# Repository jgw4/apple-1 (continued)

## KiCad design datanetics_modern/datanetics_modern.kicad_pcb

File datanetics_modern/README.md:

# Replica Datanetics Keyboard

Do you need a Datanetics ASCII keyboard for your computer project (such as a replica Apple 1)? Don't want to pay high prices for an original Datanetics keyboard? Then consider building this replica.

This is not the first replica Datanetics keyboard. Mike Willegal [designed one](http://www.willegal.net/appleii/apple1-datanetics.htm). In fact, I started with his design and redid it using KiCad. Instead of using the expensive, fragile, and hard-to-find MM5740 keyboard chip, I switched to a more common microcontroller: the ATMega644P. I also removed the output buffer chips--just in case you want to redo my firmware and implement some other keyboard protocol, you'll be able to control the pin direction.

Here are the design files. The BOM does not include manufacturer part numbers because it uses very common through hole parts that you might already have. The key switches are standard Cherry MX and are available from a wide variety of sources.

[Schematic](https://github.com/schlae/replica-datanetics/blob/main/Apple1Keyb.pdf)

[Bill of Materials](https://github.com/schlae/replica-datanetics/blob/main/Apple1Keyb.csv)

[Fab Files](https://github.com/schlae/replica-datanetics/blob/main/fab/Apple1Keyb_Rev1.zip)

[Water Slide Decal Graphics](https://github.com/schlae/replica-datanetics/blob/main/keycaps.svg)

## Fabrication and Assembly Notes

The circuit board is a 2-layer board, 11.75 by 5.5 inches (298.5 x 139.7mm). No special edge connector plating or bevel is needed. To make the board look like the original, order the board "bare bones" with no solder mask or silkscreen.

**Caution: There is a "matrix" via area in the upper left corner of the board with 76 non-plated vias. The drill locations for these are included in the "Apple1Keyb-NPTH.drl" file in the fab package. The User Comments layer also includes a note to the fab vendor to NOT plate these holes. You may want to add an extra comment to your fab vendor when you put in the order that these 76 holes must not be plated.**

To assemble the board, just solder in the components. I'd recommend using a socket for the U1 microcontroller so that you can reprogram it later. The NE555 timer (U2) in the original design was meant to provide the clock for the MM5740 chip, but isn't necessary in this design. You can install it or leave it out.

The second NE555 timer (U3) is necessary for the key repeat function.

## Key Caps

The keyboard design uses standard Cherry MX key switches and keycaps are available from numerous sources. For my own build, I used DSA keycaps along with an 8U spacebar from PMK. I looked into a number of ways of putting the legends on the keycaps but I ended up having some water slide decals custom made. See the file above if you want to use this same file, but I'd recommend putting the legends closer together so they'll fit on a smaller sheet, saving you money.

## Matrix Via Area

The Datanetics design has four key switches that are not connected to the key scanning matrix and are brought out to individual pins on the edge connector. If you're building an Apple 1, you'll want to use two of these keys for the reset and clear screen functions. 

If you want keys to be included in the scanning matrix, you'll want to solder a fine wire through the appropriate via in the upper left corner of the board. To find out which key will be generated, look up the row and column number in the key\_rom array in firmware source code. You can, of course, customize the generated key by editing the source and recompiling.

## Firmware

The firmware is designed for the ATMega644P microcontroller, but it should be possible to modify it to work with other 40-pin microcontrollers in the ATMega family. The prebuilt firmware behaves like a stock MM5740.

[Prebuilt Firmware](https://github.com/schlae/replica-datanetics/blob/main/fw/apple1keyb.hex)

Be sure to set the fuse bits of the ATMega644P according to the fuses.conf file:

```
lfuse = 0x62
hfuse = 0xdd
efuse = 0xfc
```

You can build the firmware yourself pretty easily. Under Ubuntu, install the `gcc-avr` package, and build the firmware by going to the directory and typing `make`.

If you have a minipro programmer (TL866 etc) you can program the device by typing `make fuses` followed by `make prog`. For this to work correctly, you'll need the [minipro software](https://gitlab.com/DavidGriffith/minipro) installed. You could also use the Windows minipro software from the manufacturer, or another programmer entirely.

## Mechanical Brackets

[Mike Willegal's site](http://www.willegal.net/appleii/apple1-datanetics.htm) has drawings for a mechanical bracket.

## Connecting to an Apple 1

If you want to connect this keyboard to an Apple 1, you can use the following wiring diagram. The connector to use is a 30-pin 0.156" edge connector, something like EDAC 305-030-520-202 or equivalent. The DIP plug is an insulation displacement connector, something like CW CWR-130-16-0001 or equivalent.

| Edge connector pin | Description | DIP plug pin |
|--------------------|-------------|--------------|
| A | No connect (was -12V) | 11 (-12V) |
| B | Data bit 6 | 7 (B6) |
| C | Data bit 5 | 6 (B5) |
| D | Data bit 4 | 2 (B4) |
| E | Data bit 1 | 5 (B1) |
| F | Data bit 2 | 4 (B2) |
| H | Data bit 3 | 3 (B3) |
| J | Reset key | 1 (Reset) |
| K | Reset key | 9 (Gnd) |
| L | No connect (was OE) | No connect |
| M | Strobe | 14 (Str) |
| N | Data bit 7 | 8 (B7) |
| P | Data bit 8 | No connect |
| R | No connect (was data bit 9) | No connect |
| S | Ground | 9 |
| 1 | No connect | |
| 2 | No connect | |
| 3 | No connect | |
| 4 | +5V | 15, 16 |
| 5 | No connect | |
| 6 | No connect | |
| 7 | No connect | |
| 8 | Extra key 4 | 12 (Clr) |
| 9 | Extra key 4 | 16 |
| 10 | Extra key 3 | |
| 11 | Extra key 3 | |
| 12 | Extra key 1 | |
| 13 | Extra key 1 | |
| 14 | Extra key 2 | |
| 15 | Extra key 2 | |

## Notes on the KiCad Files
The PCB file uses the plug-in library for Cherry MX keyswitches

## License
This work is licensed under a Creative Commons Attribution-ShareAlike 4.0
International License. See [https://creativecommons.org/licenses/by-sa/4.0/](https://creativecommons.org/licenses/by-sa/4.0/).

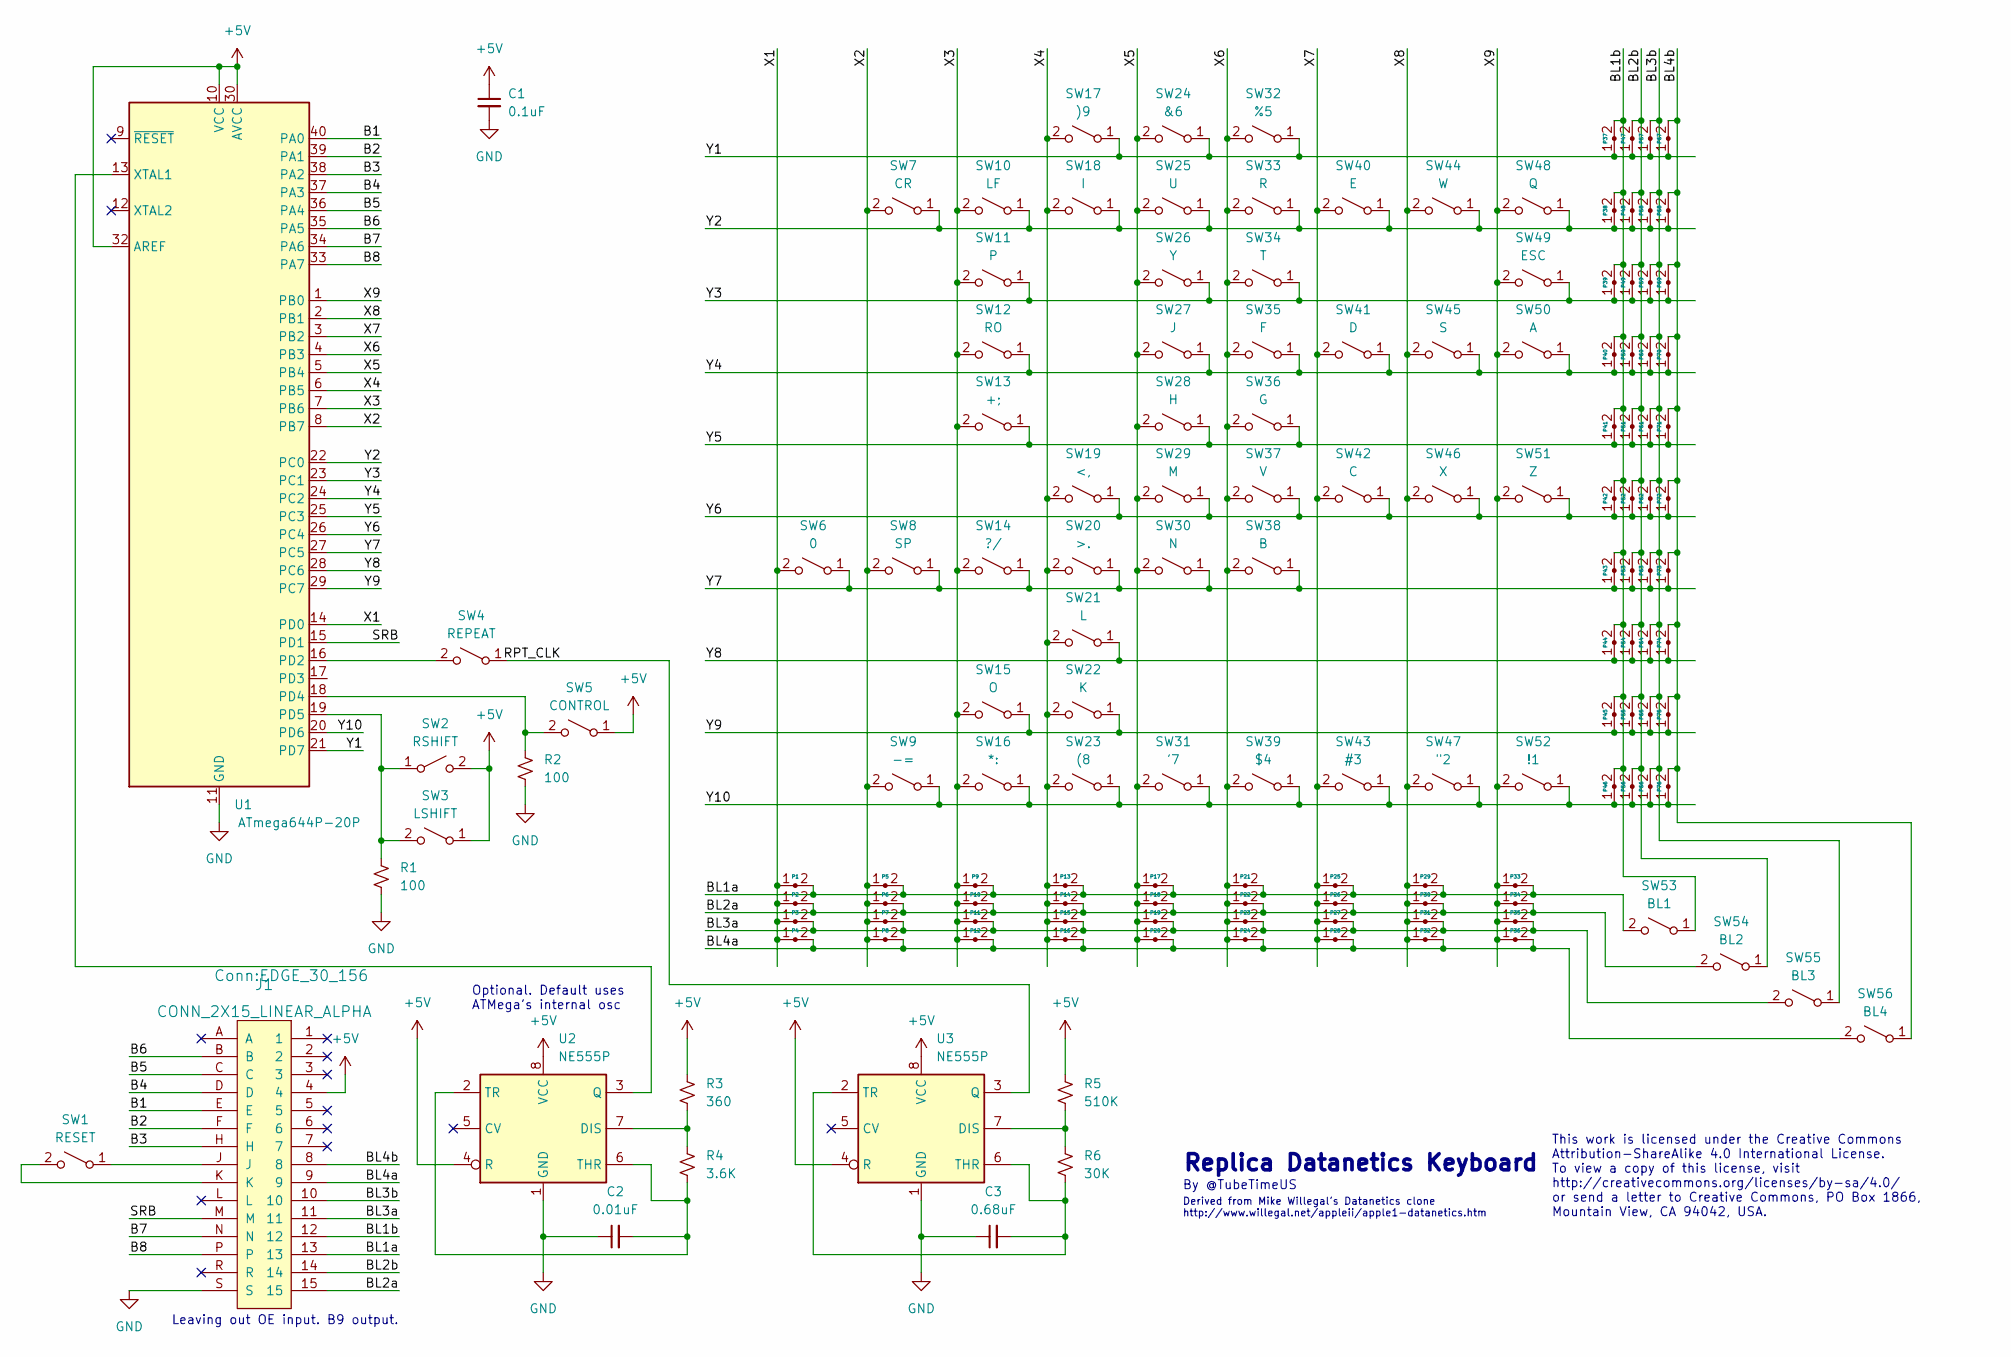
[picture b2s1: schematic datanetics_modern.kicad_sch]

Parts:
C1: 0.1uF; C_Disc_D0.2in_W0.1in_P0.2in
C2: 0.01uF; C_Disc_D0.2in_W0.1in_P0.2in
C3: 0.68uF; C_Disc_D0.2in_W0.1in_P0.2in
J1: CONN_2X15_LINEAR_ALPHA; EDGE_30_156
P1, P2, P3, P4, P5, P6, P7, P8, P9, P10, P11, P12, P13, P14, P15, P16, P17, P18, P19, P20, P21, P22, P23, P24, P25, P26, P27, P28, P29, P30, P31, P32, P33, P34, P35, P36, P37, P38, P39, P40, P41, P42, P43, P44, P45, P46, P47, P48, P49, P50, P51, P52, P53, P54, P55, P56, P57, P58, P59, P60, P61, P62, P63, P64, P65, P66, P67, P68, P69, P70, P71, P72, P73, P74, P75, P76: jumper_pth; ViaNoPlate
R1, R2: 100; RESA500
R3: 360; RESA500
R4: 3.6K; RESA500
R5: 510K; RESA500
R6: 30K; RESA500
SW1: RESET; dn_SW_Cherry_MX_PCB
SW2: RSHIFT; dn_SW_Cherry_MX_PCB
SW3: LSHIFT; dn_SW_Cherry_MX_PCB
SW4: REPEAT; dn_SW_Cherry_MX_PCB
SW5: CONTROL; dn_SW_Cherry_MX_PCB
SW6: 0; dn_SW_Cherry_MX_PCB
SW7: CR; dn_SW_Cherry_MX_PCB
SW8: SP; dn_SW_Cherry_MX_PCB_SPACEBAR
SW9: -=; dn_SW_Cherry_MX_PCB
SW10: LF; dn_SW_Cherry_MX_PCB
SW11: P; dn_SW_Cherry_MX_PCB
SW12: RO; dn_SW_Cherry_MX_PCB
SW13: +;; dn_SW_Cherry_MX_PCB
SW14: ?/; dn_SW_Cherry_MX_PCB
SW15: O; dn_SW_Cherry_MX_PCB
SW16: *:; dn_SW_Cherry_MX_PCB
SW17: )9; dn_SW_Cherry_MX_PCB
SW18: I; dn_SW_Cherry_MX_PCB
SW19: <,; dn_SW_Cherry_MX_PCB
SW20: >.; dn_SW_Cherry_MX_PCB
SW21: L; dn_SW_Cherry_MX_PCB
SW22: K; dn_SW_Cherry_MX_PCB
SW23: (8; dn_SW_Cherry_MX_PCB
SW24: &6; dn_SW_Cherry_MX_PCB
SW25: U; dn_SW_Cherry_MX_PCB
SW26: Y; dn_SW_Cherry_MX_PCB
SW27: J; dn_SW_Cherry_MX_PCB
SW28: H; dn_SW_Cherry_MX_PCB
SW29: M; dn_SW_Cherry_MX_PCB
SW30: N; dn_SW_Cherry_MX_PCB
SW31: '7; dn_SW_Cherry_MX_PCB
SW32: %5; dn_SW_Cherry_MX_PCB
SW33: R; dn_SW_Cherry_MX_PCB
SW34: T; dn_SW_Cherry_MX_PCB
SW35: F; dn_SW_Cherry_MX_PCB
SW36: G; dn_SW_Cherry_MX_PCB
SW37: V; dn_SW_Cherry_MX_PCB
SW38: B; dn_SW_Cherry_MX_PCB
SW39: $4; dn_SW_Cherry_MX_PCB
SW40: E; dn_SW_Cherry_MX_PCB
SW41: D; dn_SW_Cherry_MX_PCB
SW42: C; dn_SW_Cherry_MX_PCB
SW43: #3; dn_SW_Cherry_MX_PCB
SW44: W; dn_SW_Cherry_MX_PCB
SW45: S; dn_SW_Cherry_MX_PCB
SW46: X; dn_SW_Cherry_MX_PCB
SW47: "2; dn_SW_Cherry_MX_PCB
SW48: Q; dn_SW_Cherry_MX_PCB
SW49: ESC; dn_SW_Cherry_MX_PCB
SW50: A; dn_SW_Cherry_MX_PCB
SW51: Z; dn_SW_Cherry_MX_PCB
SW52: !1; dn_SW_Cherry_MX_PCB
SW53: BL1; dn_SW_Cherry_MX_PCB
SW54: BL2; dn_SW_Cherry_MX_PCB
SW55: BL3; dn_SW_Cherry_MX_PCB
SW56: BL4; dn_SW_Cherry_MX_PCB
U1: ATmega644P-20P; DIP-40_W15.24mm
U2, U3: NE555P; DIP-8_W7.62mm

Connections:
+5V: C1.1, J1.4, R3.2, R5.2, SW2.2 (B), SW3.1 (A), SW5.1 (A), U1.10 (VCC), U1.30 (AVCC), U1.32 (AREF), U2.4 (R), U2.8 (VCC), U3.4 (R), U3.8 (VCC)
/B1: J1.E, U1.40 (PA0)
/B2: J1.F, U1.39 (PA1)
/B3: J1.H, U1.38 (PA2)
/B4: J1.D, U1.37 (PA3)
/B5: J1.C, U1.36 (PA4)
/B6: J1.B, U1.35 (PA5)
/B7: J1.N, U1.34 (PA6)
/B8: J1.P, U1.33 (PA7)
/BL1a: J1.13, P1.2, P5.2, P9.2, P13.2, P17.2, P21.2, P25.2, P29.2, P33.2, SW53.2 (B)
/BL1b: J1.12, P37.2, P38.2, P39.2, P40.2, P41.2, P42.2, P43.2, P44.2, P45.2, P46.2, SW53.1 (A)
/BL2a: J1.15, P2.2, P6.2, P10.2, P14.2, P18.2, P22.2, P26.2, P30.2, P34.2, SW54.2 (B)
/BL2b: J1.14, P47.2, P48.2, P49.2, P50.2, P51.2, P52.2, P53.2, P54.2, P55.2, P56.2, SW54.1 (A)
/BL3a: J1.11, P3.2, P7.2, P11.2, P15.2, P19.2, P23.2, P27.2, P31.2, P35.2, SW55.2 (B)
/BL3b: J1.10, P57.2, P58.2, P59.2, P60.2, P61.2, P62.2, P63.2, P64.2, P65.2, P66.2, SW55.1 (A)
/BL4a: J1.9, P4.2, P8.2, P12.2, P16.2, P20.2, P24.2, P28.2, P32.2, P36.2, SW56.2 (B)
/BL4b: J1.8, P67.2, P68.2, P69.2, P70.2, P71.2, P72.2, P73.2, P74.2, P75.2, P76.2, SW56.1 (A)
/RPT_CLK: SW4.1 (A), U3.3 (Q)
/SRB: J1.M, U1.15 (PD1)
/X1: P1.1, P2.1, P3.1, P4.1, SW6.2 (B), U1.14 (PD0)
/X2: P5.1, P6.1, P7.1, P8.1, SW7.2 (B), SW8.2 (B), SW9.2 (B), U1.8 (PB7)
/X3: P9.1, P10.1, P11.1, P12.1, SW10.2 (B), SW11.2 (B), SW12.2 (B), SW13.2 (B), SW14.2 (B), SW15.2 (B), SW16.2 (B), U1.7 (PB6)
/X4: P13.1, P14.1, P15.1, P16.1, SW17.2 (B), SW18.2 (B), SW19.2 (B), SW20.2 (B), SW21.2 (B), SW22.2 (B), SW23.2 (B), U1.6 (PB5)
/X5: P17.1, P18.1, P19.1, P20.1, SW24.2 (B), SW25.2 (B), SW26.2 (B), SW27.2 (B), SW28.2 (B), SW29.2 (B), SW30.2 (B), SW31.2 (B), U1.5 (PB4)
/X6: P21.1, P22.1, P23.1, P24.1, SW32.2 (B), SW33.2 (B), SW34.2 (B), SW35.2 (B), SW36.2 (B), SW37.2 (B), SW38.2 (B), SW39.2 (B), U1.4 (PB3)
/X7: P25.1, P26.1, P27.1, P28.1, SW40.2 (B), SW41.2 (B), SW42.2 (B), SW43.2 (B), U1.3 (PB2)
/X8: P29.1, P30.1, P31.1, P32.1, SW44.2 (B), SW45.2 (B), SW46.2 (B), SW47.2 (B), U1.2 (PB1)
/X9: P33.1, P34.1, P35.1, P36.1, SW48.2 (B), SW49.2 (B), SW50.2 (B), SW51.2 (B), SW52.2 (B), U1.1 (PB0)
/Y1: P37.1, P47.1, P57.1, P67.1, SW17.1 (A), SW24.1 (A), SW32.1 (A), U1.21 (PD7)
/Y2: P38.1, P48.1, P58.1, P68.1, SW7.1 (A), SW10.1 (A), SW18.1 (A), SW25.1 (A), SW33.1 (A), SW40.1 (A), SW44.1 (A), SW48.1 (A), U1.22 (PC0)
/Y3: P39.1, P49.1, P59.1, P69.1, SW11.1 (A), SW26.1 (A), SW34.1 (A), SW49.1 (A), U1.23 (PC1)
/Y4: P40.1, P50.1, P60.1, P70.1, SW12.1 (A), SW27.1 (A), SW35.1 (A), SW41.1 (A), SW45.1 (A), SW50.1 (A), U1.24 (PC2)
/Y5: P41.1, P51.1, P61.1, P71.1, SW13.1 (A), SW28.1 (A), SW36.1 (A), U1.25 (PC3)
/Y6: P42.1, P52.1, P62.1, P72.1, SW19.1 (A), SW29.1 (A), SW37.1 (A), SW42.1 (A), SW46.1 (A), SW51.1 (A), U1.26 (PC4)
/Y7: P43.1, P53.1, P63.1, P73.1, SW6.1 (A), SW8.1 (A), SW14.1 (A), SW20.1 (A), SW30.1 (A), SW38.1 (A), U1.27 (PC5)
/Y8: P44.1, P54.1, P64.1, P74.1, SW21.1 (A), U1.28 (PC6)
/Y9: P45.1, P55.1, P65.1, P75.1, SW15.1 (A), SW22.1 (A), U1.29 (PC7)
/Y10: P46.1, P56.1, P66.1, P76.1, SW9.1 (A), SW16.1 (A), SW23.1 (A), SW31.1 (A), SW39.1 (A), SW43.1 (A), SW47.1 (A), SW52.1 (A), U1.20 (PD6)
GND: C1.2, C2.1, C3.1, J1.S, R1.1, R2.1, U1.11 (GND), U1.31 (GND), U2.1 (GND), U3.1 (GND)
unnamed: J1.J, SW1.1 (A)
unnamed: J1.K, SW1.2 (B)
unnamed: R1.2, SW2.1 (A), SW3.2 (B), U1.19 (PD5)
unnamed: SW4.2 (B), U1.16 (PD2)
unnamed: R2.2, SW5.2 (B), U1.18 (PD4)
unnamed: U1.13 (XTAL1), U2.3 (Q)
unnamed: R3.1, R4.2, U2.7 (DIS)
unnamed: C2.2, R4.1, U2.2 (TR), U2.6 (THR)
unnamed: R5.1, R6.2, U3.7 (DIS)
unnamed: C3.2, R6.1, U3.2 (TR), U3.6 (THR)

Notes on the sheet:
By @TubeTimeUS
Leaving out OE input. B9 output.
Optional. Default uses ATMega's internal osc
Derived from Mike Willegal's Datanetics clone http://www.willegal.net/appleii/apple1-datanetics.htm
Replica Datanetics Keyboard
This work is licensed under the Creative Commons Attribution-ShareAlike 4.0 International License. To view a copy of this license, visit http://creativecommons.org/licenses/by-sa/4.0/ or send a letter to Creative Commons, PO Box 1866, Mountain View, CA 94042, USA.

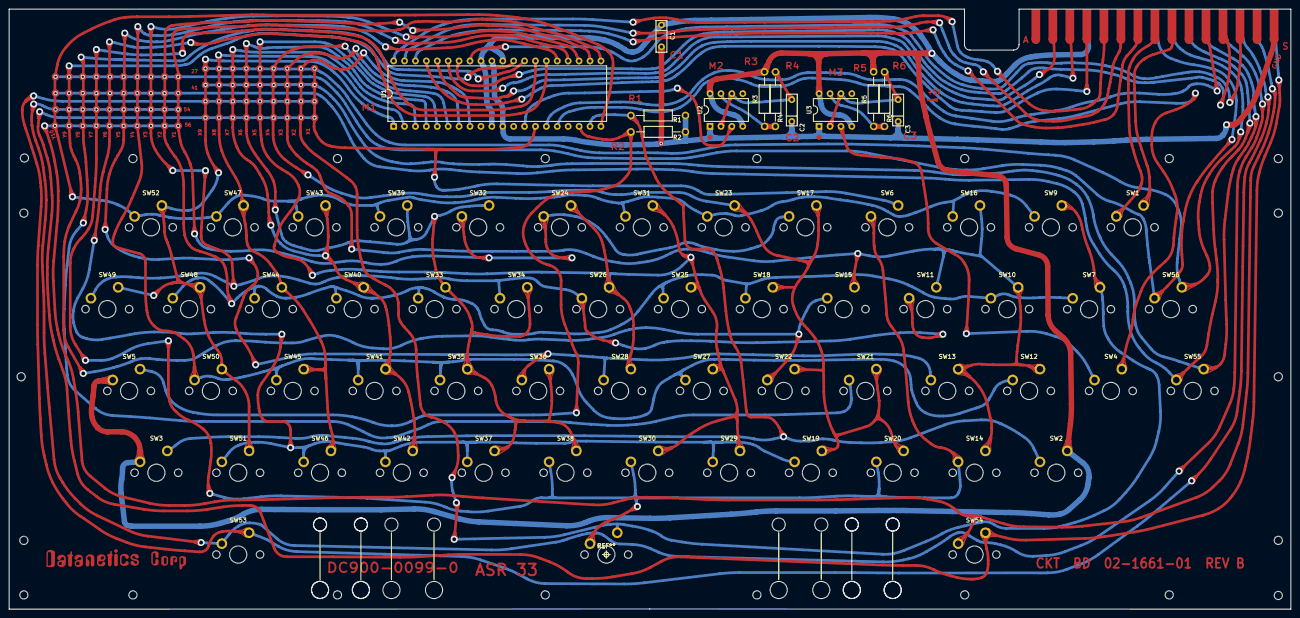
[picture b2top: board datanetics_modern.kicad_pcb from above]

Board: 2 copper layers, 298.4 x 139.7 mm, 169 parts (1 on the bottom side), 49 nets.

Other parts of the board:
G1: LOGO; Datanetics
MH1, MH2, MH3, MH4, MH5, MH6, MH7, MH8, MH9, MH10, MH11, MH12, MH13, MH14, MH15, MH16, MH17, MH18, MH19, MH20, MH21, MH22: MountHole
ST1: CHERRY_ST3

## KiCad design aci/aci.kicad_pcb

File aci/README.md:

# Cassette Interface

The Apple Cassette Interface "ACI" card has been completely reverse-engineered in KiCad 10, with linked KiCad and schematic files, which output production-ready gerber files and a fully-populated step file of the card with components.

The PCB File was made by importing gerber files for "PCB-07" first into KiCad, and mapping the schematics to it by applying footprints to the symbols, placing over the gerber geometry, and then removing the import gerber geometry

The Board is 100% complete and ready for production. gerber files are available in the /gerbers/ folder

## Changes from PCB-07

* the soldermask on the gold contact fingers has been extended slightly upward into the full board width
* pads have been redone from circles to ovals/ squashed obrounds in the same style as /mainboard
* the inside corner between the edge connector and the card was sharp, it is now radiused to reflect the original

## Known deviations from the original
* there is no manufacturer logo on the part as of now.
* I have not done enough research on this card yet to determine if this is a 1st rev version or a second rev version. I would like this card to be the second revision if it is not already.

## Ordering
* as with the mainboard, make sure to order soldermask in a matte or light green finish
* there are some silkscreen remnants on the KiCad file, but they are not to be used in production. Do not send silkscreen files to the Manufacturer!
* For the most historical accuracy, specify hard gold on the edge connector. It adds cost, but

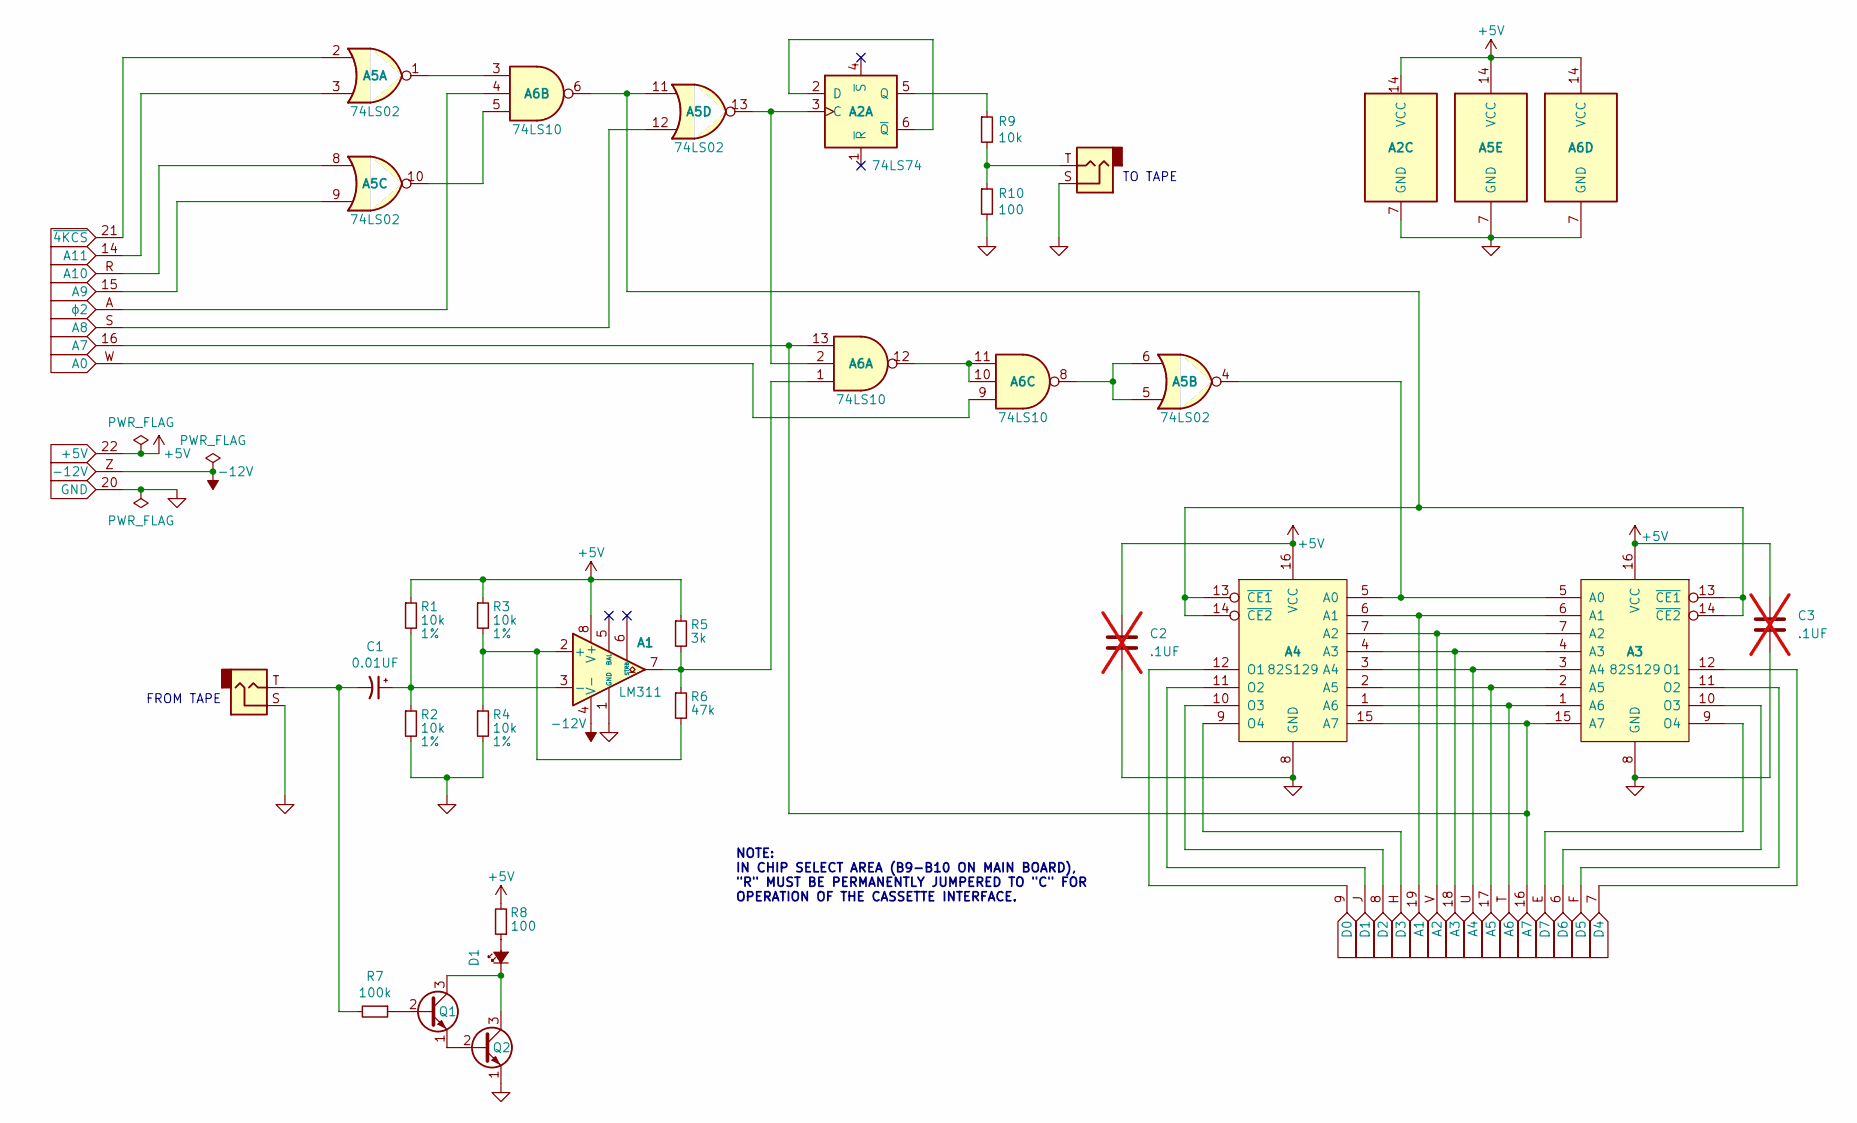
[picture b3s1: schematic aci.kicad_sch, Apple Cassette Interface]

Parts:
A1: LM311; apple-1_DIP-8_W7.62mm
A2: 74LS74; apple-1_DIP-14_W7.62mm
A3, A4: 82S129; apple-1_DIP-16_W7.62mm
A5: 74LS02; apple-1_DIP-14_W7.62mm
A6: 74LS10; apple-1_DIP-14_W7.62mm
C1: 0.01UF; C_Disc_.01_p350MILS
C2, C3: .1UF; C_AxialDecoupling; not fitted
D1: LED_Small_ALT; LED_D4.0mm
J1: Switchcraft #41; aci_phonopads_frmtape
J2: Switchcraft #41; aci_phonopads
J3: ACI_EdgeConnector; aci_edgecon
Q1, Q2: Q_NPN_EBC; aci_TO-92_bent
R1, R2, R3, R4: 10k; R_Axial_ACI; Tolerance 1%
R5: 3k; R_Axial_ACI
R6: 47k; R_Axial_ACI
R7: 100k; R_Axial_ACI
R8, R10: 100; R_Axial_ACI
R9: 10k; R_Axial_ACI

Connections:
+5V: A1.8 (V+), A2.14 (VCC), A3.16 (VCC), A4.16 (VCC), A5.14 (VCC), A6.14 (VCC), C2.1, C3.1, J3.22 (+5V), R1.1, R3.1, R5.1, R8.2
-12V: A1.4 (V-), J3.Z (-12V)
GND: A1.1 (GND), A2.7 (GND), A3.8 (GND), A4.8 (GND), A5.7 (GND), A6.7 (GND), C2.2, C3.2, J1.S, J2.S, J3.20 (GND), Q2.1 (E), R2.2, R4.2, R10.2
unnamed: A1.2 (+), R3.2, R4.1, R6.2
unnamed: A1.3 (-), C1.1, R1.2, R2.1
unnamed: A1.7, A6.1, R5.2, R6.1
unnamed: A2.3 (C), A5.13, A6.2
unnamed: A2.2 (D), A2.6 (~Q)
unnamed: A2.5 (Q), R9.1
unnamed: A3.5 (A0), A4.5 (A0), A5.4
unnamed: A3.6 (A1), A4.6 (A1), J3.19 (A1)
unnamed: A3.7 (A2), A4.7 (A2), J3.V (A2)
unnamed: A3.4 (A3), A4.4 (A3), J3.18 (A3)
unnamed: A3.3 (A4), A4.3 (A4), J3.U (A4)
unnamed: A3.2 (A5), A4.2 (A5), J3.17 (A5)
unnamed: A3.1 (A6), A4.1 (A6), J3.T (A6)
unnamed: A3.15 (A7), A4.15 (A7), A6.13, J3.16 (A7)
unnamed: A3.12 (O1), J3.7 (D4)
unnamed: A3.11 (O2), J3.F (D5)
unnamed: A3.10 (O3), J3.6 (D6)
unnamed: A3.9 (O4), J3.E (D7)
unnamed: A3.13 (~CE1), A3.14 (~CE2), A4.13 (~CE1), A4.14 (~CE2), A5.11, A6.6
unnamed: A4.12 (O1), J3.9 (D0)
unnamed: A4.11 (O2), J3.J (D1)
unnamed: A4.10 (O3), J3.8 (D2)
unnamed: A4.9 (O4), J3.H (D3)
unnamed: A5.1, A6.3
unnamed: A5.5, A5.6, A6.8
unnamed: A5.10, A6.5
unnamed: A6.10, A6.11, A6.12
unnamed: C1.2, J1.T, R7.2
unnamed: D1.2 (A), R8.1
unnamed: D1.1 (K), Q1.3 (C), Q2.3 (C)
unnamed: J2.T, R9.2, R10.1
unnamed: A6.9, J3.W (A0)
unnamed: A5.12, J3.S (A8)
unnamed: A5.9, J3.15 (A9)
unnamed: A5.8, J3.R (A10)
unnamed: A5.3, J3.14 (A11)
unnamed: A5.2, J3.21 (~4KCS)
unnamed: A6.4, J3.A (ɸ2)
unnamed: Q1.2 (B), R7.1
unnamed: Q1.1 (E), Q2.2 (B)

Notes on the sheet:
FROM TAPE
NOTE: IN CHIP SELECT AREA (B9-B10 ON MAIN BOARD), "R" MUST BE PERMANENTLY JUMPERED TO "C" FOR OPERATION OF THE CASSETTE INTERFACE.
TO TAPE

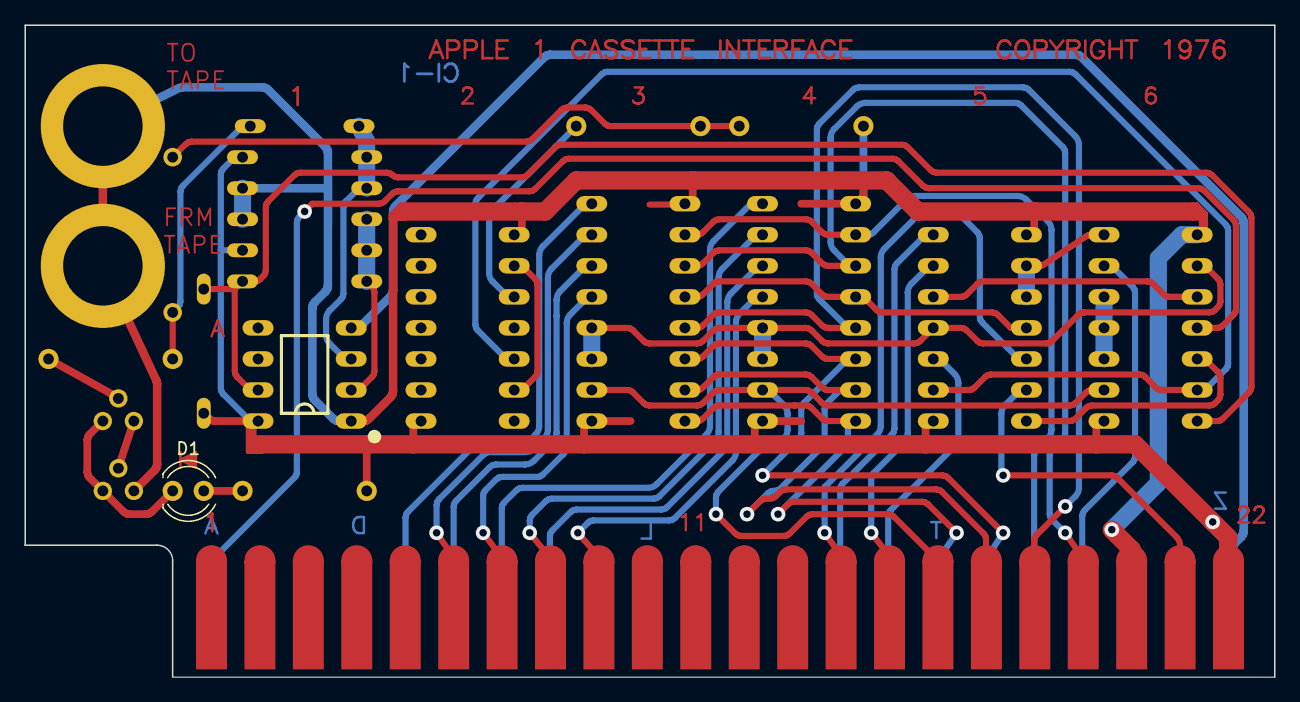
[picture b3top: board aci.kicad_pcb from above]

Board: 2 copper layers, 102.2 x 53.3 mm, 23 parts (0 on the bottom side), 43 nets.

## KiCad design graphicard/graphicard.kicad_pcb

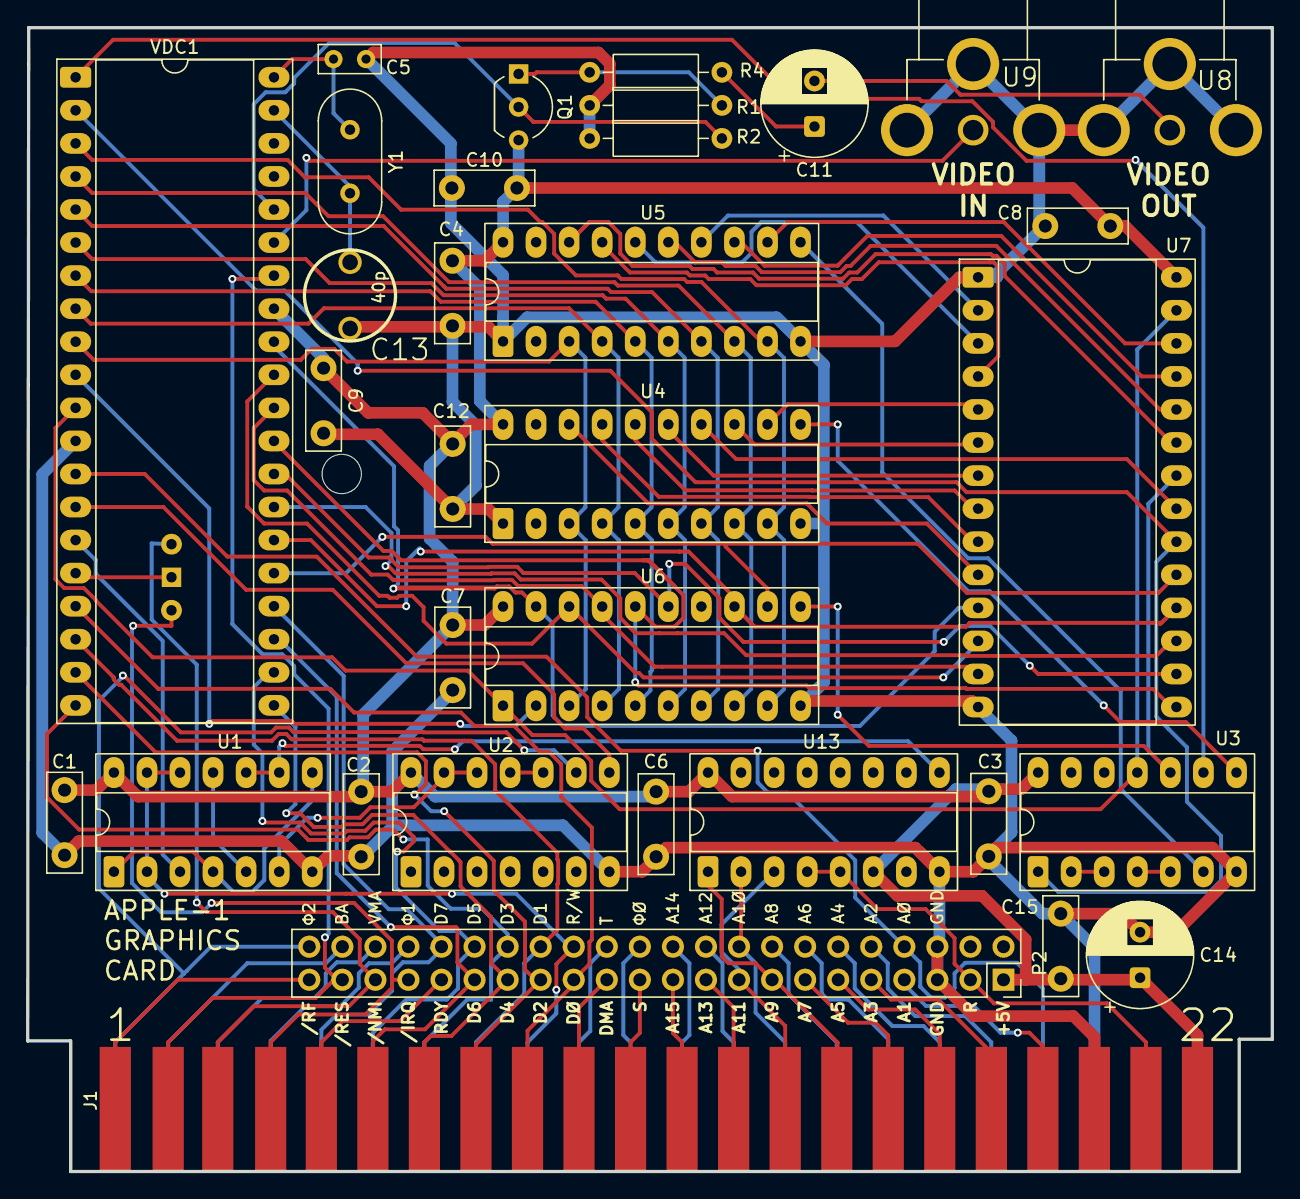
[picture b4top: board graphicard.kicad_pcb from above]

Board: 2 copper layers, 95.6 x 87.9 mm, 34 parts (1 on the bottom side), 82 nets.

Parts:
C1, C2, C3, C4, C6, C7, C8, C9, C10, C12, C15: 100nF; C_Disc_D7.5mm_W2.5mm_P5.00mm
C5: 22pF; C_Rect_L4.6mm_W2.0mm_P2.50mm_MKS02_FKP02
C11, C14: 220uF; CP_Radial_D8.0mm_P3.50mm
C13: 40p; MINIATURE 6MM TRIMMER CAPACITOR BY PANASONIC
IRQ/NMI1: HEADERDIP3HEADERDIP3; SW_Slide-03_Wuerth-WS-SLTV_10x2.5x6.4_P2.54mm
J1: Apple-1 Expansion connector; edgeconnector
P2: Header-Female-2.54_2x22; PinSocket_2x22_P2.54mm_Vertical
Q1: 2N2222A; TO-92_Inline_Wide
R1: 75 1/4W; R_Axial_DIN0207_L6.3mm_D2.5mm_P10.16mm_Horizontal
R2: 470 1/4W; R_Axial_DIN0207_L6.3mm_D2.5mm_P10.16mm_Horizontal
R4: 1/4W RESISTOR; R_Axial_DIN0207_L6.3mm_D2.5mm_P10.16mm_Horizontal
U1, U2: MC74HC00AN; DIP-14_W7.62mm_Socket_LongPads
U3: SN74HCT04N; DIP-14_W7.62mm_Socket_LongPads
U4, U5, U6: SN74HC574N; DIP-20_W7.62mm_Socket_LongPads
U7: 62256; DIP-28_W15.24mm_Socket_LongPads
U8: OUT; KEYSTONE_900
U9: IN; KEYSTONE_900
U13: SN74HCT138DR; DIP-16_W7.62mm_Socket_LongPads
VDC1: TMS9918A; DIP-40_W15.24mm_Socket_LongPads
Y1: 10.738635; Crystal_HC49-U_Vertical

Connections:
+5V: C1.1, C2.1, C3.1, C4.1, C6.1, C7.1, C8.1, C9.1, C10.1, C12.2, C14.1, C15.1, P2.1, U1.14 (VCC), U2.14 (VCC), U3.14 (VCC), U4.20 (VCC), U5.20 (VCC), U6.20 (VCC), U7.28 (VCC), U13.6 (G1), U13.16 (VCC), VDC1.33 (VCC)
A0_BUS: J1.D (W), P2.8, VDC1.13 (MODE)
A2_BUS: J1.E (V), P2.10
A4_BUS: J1.F (U), P2.12
A8_BUS: J1.H (S), P2.16
A9_BUS: P2.15, U13.1 (A)
A10_BUS: P2.18, U13.2 (B)
A11_BUS: P2.17, U13.3 (C)
A12_BUS: J1.J, P2.20
A14_BUS: J1.K (N), P2.22
AD0: U6.2 (1D), VDC1.10 (AD0)
AD1: U4.3 (2D), U5.3 (2D), U6.3 (2D), VDC1.9 (AD1)
AD2: U4.4 (3D), U5.4 (3D), U6.4 (3D), VDC1.8 (AD2)
AD3: U4.5 (4D), U5.5 (4D), U6.5 (4D), VDC1.7 (AD3)
AD4: U4.6 (5D), U5.6 (5D), U6.6 (5D), VDC1.6 (AD4)
AD5: U4.7 (6D), U5.7 (6D), U6.7 (6D), VDC1.5 (AD5)
AD6: U4.8 (7D), U5.8 (7D), U6.8 (7D), VDC1.4 (AD6)
AD7: U4.9 (8D), U5.9 (8D), U6.9 (8D), VDC1.3 (AD7)
BA_BUS: J1.U (B), P2.42
CAS: U3.1 (1A), U7.20 (~E), VDC1.2 (!CAS)
CC: U1.9, U1.10, U13.9 (Y6)
COL: U3.6 (3Y), U5.11 (CLK)
COMVID: R2.1, VDC1.36 (Y)
D0_BUS: P2.27, VDC1.17 (CD7)
D1_BUS: P2.30, VDC1.18 (CD6)
D2_BUS: P2.29, VDC1.19 (CD5)
D3_BUS: J1.P (H), P2.32, VDC1.20 (CD4)
D4_BUS: P2.31, VDC1.21 (CD3)
D5_BUS: P2.34, VDC1.22 (CD2)
D6_BUS: P2.33, VDC1.23 (CD1)
D7_BUS: J1.R (E), P2.36, VDC1.24 (CD0)
GND: C1.2, C2.2, C3.2, C4.2, C5.2, C6.2, C7.2, C8.2, C9.2, C10.2, C12.1, C13.2, C14.2, C15.2, J1.C (X), P2.5, P2.6, R1.2, R2.2, U1.7 (GND), U2.7 (GND), U3.7 (GND), U4.1 (OE#), U4.10 (GND), U5.1 (OE#), U5.10 (GND), U6.10 (GND), U7.1 (A14), U7.14 (VSS), U8.S1, U8.S2, U8.S3, U9.S1, U9.S2, U9.S3, U13.8 (GND), VDC1.12 (VSS)
IRQ_BUS: IRQ/NMI1.3, P2.37
NMI_BUS: IRQ/NMI1.1, P2.39
unnamed: C11.1, R4.1
unnamed: C11.2, U8.1
unnamed: R1.1, R4.2
unnamed: U1.1, U1.4, U1.8
unnamed: U1.6, U2.12, U2.13
unnamed: U1.5, U1.11
unnamed: U2.10, U2.11
unnamed: U3.2 (1Y), U3.3 (2A)
unnamed: U3.4 (2Y), U3.5 (3A)
unnamed: U1.3, VDC1.15 (!CSR)
unnamed: U2.8, VDC1.14 (!CSW)
unnamed: IRQ/NMI1.2, VDC1.16 (!INT)
unnamed: U9.1, VDC1.35 (B-Y)
unnamed: C13.1, VDC1.39 (XTAL1), Y1.2
unnamed: C5.1, VDC1.40 (XTAL2), Y1.1
PHI0_BUS: J1.L (M), P2.24
PHI1_BUS: J1.S (D), P2.38
Phi2_BUS: J1.V (A), P2.40 (44), U2.9
R*_BUS: P2.3, U13.4 (G#2A), U13.5 (G#2B)
RAS: U3.9 (4A), VDC1.1 (!RAS)
ROW: U3.8 (4Y), U4.11 (CLK)
R/W_BUS: J1.N (K), P2.28, U1.2, U1.12, U1.13
T*_BUS: J1.M (L), P2.26
VA0: U4.18 (2Q), U7.10 (A0)
VA1: U4.17 (3Q), U7.9 (A1)
VA2: U4.16 (4Q), U7.8 (A2)
VA3: U4.15 (5Q), U7.7 (A3)
VA4: U4.14 (6Q), U7.21 (A10)
VA5: U4.13 (7Q), U7.6 (A4)
VA6: U4.12 (8Q), U7.5 (A5)
VA7: U5.18 (2Q), U7.23 (A11)
VA8: U5.17 (3Q), U7.4 (A6)
VA9: U5.16 (4Q), U7.3 (A7)
VA10: U5.15 (5Q), U7.24 (A9)
VA11: U5.14 (6Q), U7.2 (A12)
VA12: U5.13 (7Q), U7.25 (A8)
VA13: U5.12 (8Q), U7.26 (A13)
VD0: U6.19 (1Q), U7.11 (Q0), VDC1.32 (RD0)
VD1: U6.18 (2Q), U7.12 (Q1), VDC1.31 (RD1)
VD2: U6.17 (3Q), U7.13 (Q2), VDC1.30 (RD2)
VD3: U6.16 (4Q), U7.15 (Q3), VDC1.29 (RD3)
VD4: U6.15 (5Q), U7.16 (Q4), VDC1.28 (RD4)
VD5: U6.14 (6Q), U7.17 (Q5), VDC1.27 (RD5)
VD6: U6.13 (7Q), U7.18 (Q6), VDC1.26 (RD6)
VD7: U6.12 (8Q), U7.19 (Q7), VDC1.25 (RD7)
VRW: U3.11 (5A), U6.1 (OE#), U7.27 (~WE), VDC1.11 (!R/W)
VWR: U3.10 (5Y), U6.11 (CLK), U7.22 (~G)
/RESET_BUS: P2.41, VDC1.34 (!RESET)

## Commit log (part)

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2026-05-21 Further work on the schematics/file organization
2026-05-22 Additional work on mainboard
2026-05-27 Progress 20260526
2026-06-01 added datanetics keyboard original + modern
2026-06-01 File reorg and creation of some kicad projects from gerber files
2026-06-01 added readmes
2026-06-02 fixes to readmes
2026-06-02 removed .prl, augmented cassette interface
2026-06-02 new file: aci/README.md modified: aci/aci.kicad_pcb new file: aci/aci.kicad_pro modified: aci/aci.kicad_sch deleted: aci/aci.pro deleted: aci/aci.sch new file: doc/apple1cassette.pdf deleted: doc/pro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
2026-06-02 large renaming, tidying up files, old libraries
2026-06-03 modified: aci/README.md modified: aci/aci.kicad_pcb modified: aci/aci.kicad_sch new file: aci/aci.pretty/aci_TO-92_bent.kicad_mod new file: aci/fp-lib-table new file: doc/aci-assembly-v0.18.pdf modif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
2026-06-03 removing overlapping footprint geometry
2026-06-05 20260605
2026-06-08 converted manuals into readmes
2026-06-30 manual work
